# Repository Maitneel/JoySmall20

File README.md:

# JoySmall20
ちょっとしたショートカットやマウス操作をすることを目的に作られた100x95.25mmのキーボードです。

20個のキーとジョイスティック、ロータリーエンコーダを搭載しています。

## Build Guide
必要な部品は以下の通りです

|部品名|個数|遊舎工房さんの商品ページ|秋月電子さんの商品ページ||
|:---|---|---|---|---|
|ProMicro|1|https://shop.yushakobo.jp/products/3905 <br> https://shop.yushakobo.jp/products/pro-micro||いずれか1つで大丈夫です。個人的にはType-Cの方がおすすめです|
|Cherry MX 互換スイッチ|0~20|||つけたい個数用意してください。ProMicroを表側につける場合は最大で18個になります|
|Kailh Switch Socket|スイッチと同じ個数|https://shop.yushakobo.jp/products/a01ps||なくても大丈夫です。MX用を購入してください|
|ダイオード (1N4148)|スイッチと同じ個数|https://shop.yushakobo.jp/products/a0800di-01-100|https://akizukidenshi.com/catalog/g/g100941/||
|ジョイスティック|1||https://akizukidenshi.com/catalog/g/g115951||
|ロータリーエンコーダー|1|https://shop.yushakobo.jp/products/3762|https://akizukidenshi.com/catalog/g/g105772/<br>https://akizukidenshi.com/catalog/g/g105769/<br>https://akizukidenshi.com/catalog/g/g105770/<br>https://akizukidenshi.com/catalog/g/g105771/|EC12と互換性があれば大丈夫だと思います。個人的にはLEDがついてるやつがおすすめです。動作確認は赤・青のLED付きのもので行ってます。1色、フルカラーのLEDが付いてるものがありますが、穴の位置、配線の実装の関係で対応できません|
|LED|0~3|||ロータリーエンコーダでLED付きのものを使用しない場合2つ、ジョイスティックのセンタープッシュを利用しない場合追加で1つのLEDをつけることができます|
|LED用抵抗|LEDと同じ個数|||使用するLEDに合わせて必要な抵抗値を計算してください|
|ジョイスティックセンタープッシュのジャンパー用抵抗|0~1|||あまりに高い抵抗値でなければなんでも大丈夫だと思います。ジャンパーできればいいのでワイヤーでも大丈夫です|
|RESET用タクトスイッチ|1|https://shop.yushakobo.jp/products/a1600ed-01-1|https://akizukidenshi.com/catalog/g/g114890/<br>https://akizukidenshi.com/catalog/g/g114891/||
|コンデンサ|0~2|||ロータリーエンコーダーのノイズ対策につけることができます。プログラムで対応する場合はつけなくて大丈夫です|
|3.5mm TRSジャック|0~1|https://shop.yushakobo.jp/products/a0800tr-01-1|https://akizukidenshi.com/catalog/g/g106070/|通信できたら面白そうだなと思って基板設計ではつけましたが、今のところ対応してないのでただの飾りになる可能性が高いです。|

### 組み立て
撮り忘れたので写真とか動画はないです。正直どの順番でやってもいいのでやりやすい順にやってください。

JoyStickとかRotaryEncoderとかのフットプリントがある方が表で、SW8, SW9から見てJoyStickがある方が上側として説明します。
適時正しく接続ができているか確認してください。

1. ダイオードを半田付けします。フットプリントが四角くなっている方がカソードです。
2. 抵抗を半田付けします。LED1, LED2, LED3に接続する抵抗がそれぞれR1, R2, R3です。LED付きのロータリーエンコーダーを使用する場合R1が基板上部よりのLEDピン、R2が基板Cherryスイッチよりのピンになります。ジョイスティックのセンタープッシュを使用する場合はR4に抵抗(またはワイヤー)を接続してください。
LED3とジョイスティックのセンタープッシュについては同じピンを使用しています。そのため同時に使用することはできませんので、R3とR4を両方とも取り付けることはしないでください。
3. Kailh Switch Socketを取り付ける場合は半田付けする
4. (つける場合は)LED, TRRSジャック, RESET用のタクトスイッチを半田付けする。
-----
ProMicroを裏面につける場合

どちらにつける場合も共通で、一番上のSW3よりのピンがTXO、一番上のJoyStickよりのピンがRAWと接続されるように半田付けします。

5. Kailh Switch Socketを使用しない場合はSW2, SW4を半田付する。(ProMicroを取り付けるのがかなり難しくなるのでSW2, SW4についてはSocketを使うことをおすすめします)
6. ProMicroにピンヘッダを半田付けする。このとき、ProMicroのUSBコネクタがある面からピンヘッダを差し込み、USBコネクタがない面から半田付してください。
7. USBコネクタが上側に来るようにProMicroを基盤に半田付けする。(ピンの位置に注意してください)
2.56mmのピンヘッダを使用し、使用する場合Socketと干渉すると思うので、長めのピンヘッダを使うか、ピンヘッダの絶縁体部分を取り外すか別のピンヘッダの絶縁体部分を用意し、端の部分を2つ重ねて高さを稼ぐなどしてください
------
ProMicroを表面につける場合

どちらにつける場合も共通で、一番上のSW3よりのピンがTXO、一番上のJoyStickよりのピンがRAWと接続されるように半田付けします。

表面に取り付ける場合SW2, SW4は使用できません。

5. ProMicroにピンヘッダを半田付けする。このとき、ProMicroのUSBコネクタのない面からピンヘッダを差し込み、USBコネクタがある面から半田付してください。
6. USBコネクタが上側に来るようにProMicroを基盤に半田付けする。(ピンの位置に注意してください)
----
8. Kailh Switch Socketを使用しない場合はCherry MX 互換スイッチを半田付けする
9. ジョイスティック, ロータリーエンコーダーを取り付ける
10. Kailh Switch Socketを取り付けた場合はスイッチをはめ込む

### ファームウェアを書き込む
今のところ自作のファームウェアしかないので、QMK Firmwareなどをを使って書き込みたい場合はいい感じに作ってください。

まず初めにキーマップを作成します。

1. [Keymap Editor](https://maitneel.github.io/JoySmall20/)でキーマップを編集します。割り当てたいキーの位置をクリックしてから割り当てたいキーをクリックすると割り当てられます。LAYERキーは押している間だけレイヤーの切り替えができます。Layoutはロータリーエンコーダーでキーマップの切り替えができます。
2. `Download define_custom_size.h`, `Download define_custom_keymap.ino`のボタンを押し、設定ファイルをダウンロードします。

キーマップの書き込みをします。Arduino IDEが必要になるので、インストールされていない場合はインストールしてください。

3. [ファームウェアのソースコード](https://github.com/Maitneel/JoySmall20/releases/latest)をダウンロードします。(Releaseから好きなものをダウンロードすることもできますが、バグがある可能性があるのでlatestをダウンロードすることをお勧めします)
4. ダウンロードしたソースコードの`define_custom_size.h`と`define_custom_keymap.ino`に2でダウンロードしたファイルに置き換えます。
5. Arduino IDEで`firmwere_srcs/JoySmall20/JoySmall20.ino`を開き、ProMicroに書き込みます。RESETを2回押すとか連打するとかすると書き込みモードになるはずなのでいろいろ試してみてください。

----

一応これで動くはずです。問題があるようでしたらissue等でご連絡ください！

### 免責
このリポジトリに存在するいずれかまたは全てのものを使用して生じたいかなる損害について、作者はいかなる責任も負いません。

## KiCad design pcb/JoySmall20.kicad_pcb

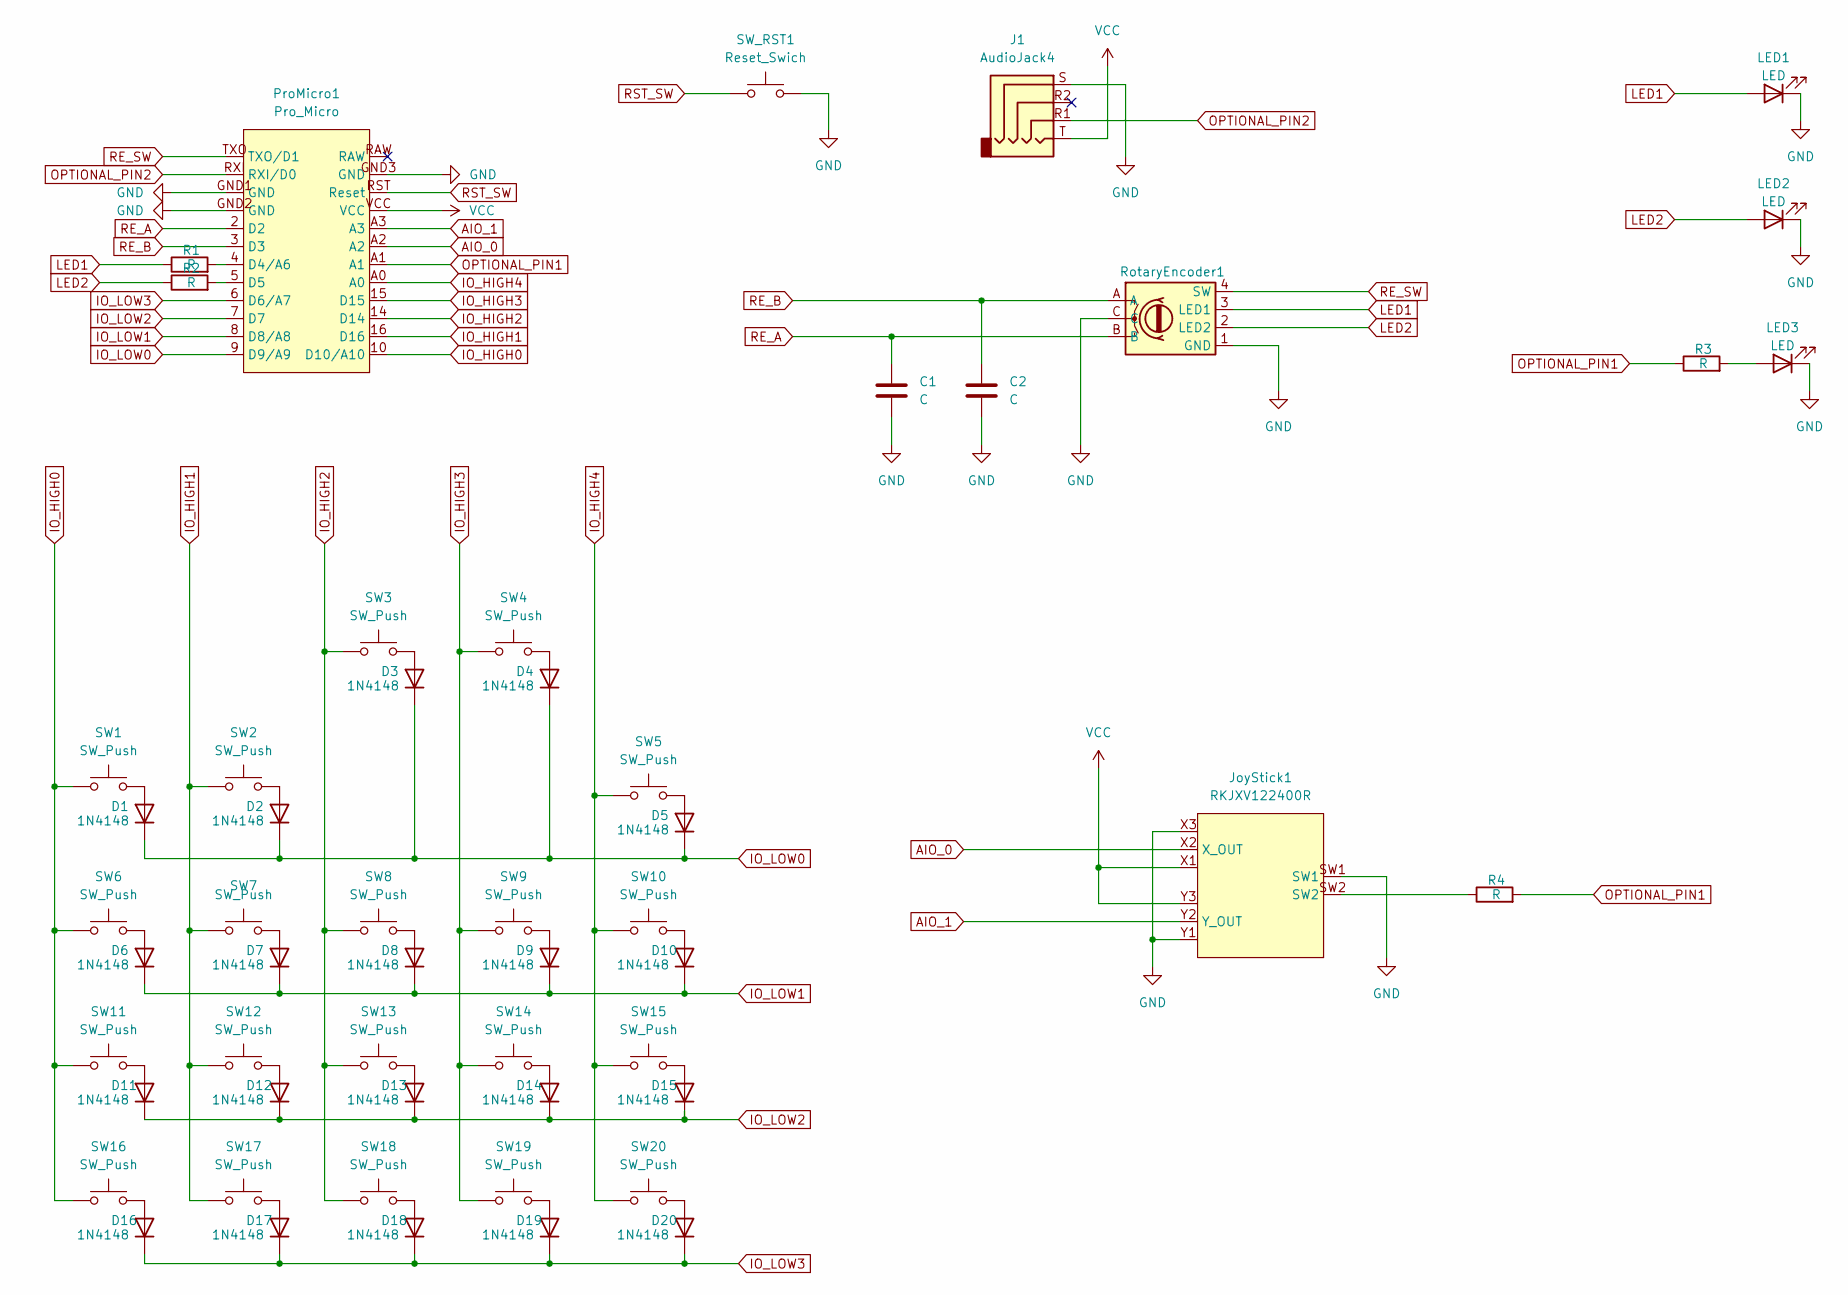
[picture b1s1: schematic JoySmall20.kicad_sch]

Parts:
C1, C2: C; C_Disc_D6.0mm_W2.5mm_P5.00mm
D1, D2, D3, D4, D5, D6, D7, D8, D9, D10, D11, D12, D13, D14, D15, D16, D17, D18, D19, D20: 1N4148
J1: AudioJack4; 3.5mm_audio_jack
JoyStick1: RKJXV122400R
LED1, LED2, LED3: LED; LED_D5.0mm
ProMicro1: Pro_Micro; Pro_Micro_small_pin
R1, R2, R3, R4: R; R_Axial_DIN0207_L6.3mm_D2.5mm_P7.62mm_Horizontal
RotaryEncoder1: RotaryEncoder_with_4pin
SW1, SW2, SW3, SW4, SW5, SW6, SW7, SW8, SW9, SW10, SW11, SW12, SW13, SW14, SW15, SW16, SW17, SW18, SW19, SW20: SW_Push; SW_Cherry_MX_1.00u_PCB_with_kalih_socket_CPG151101S11-16
SW_RST1: Reset_Swich; SW_TactSwitch_THBP07-043CB

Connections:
AIO_0: JoyStick1.X2 (X_OUT), ProMicro1.A2
AIO_1: JoyStick1.Y2 (Y_OUT), ProMicro1.A3
DATA: J1.R1, ProMicro1.RXI (RXI/D0)
GND: C1.2, C2.2, J1.S, JoyStick1.SW1, JoyStick1.X3, JoyStick1.Y1, LED1.1 (K), LED2.1 (K), LED3.1 (K), ProMicro1.GND1 (GND), ProMicro1.GND2 (GND), ProMicro1.GND3 (GND), RotaryEncoder1.1 (GND), RotaryEncoder1.C, SW_RST1.2
IO_HIGH0: ProMicro1.10 (D10/A10), SW1.1, SW6.1, SW11.1, SW16.1
IO_HIGH1: ProMicro1.16 (D16), SW2.1, SW7.1, SW12.1, SW17.1
IO_HIGH2: ProMicro1.14 (D14), SW3.1, SW8.1, SW13.1, SW18.1
IO_HIGH3: ProMicro1.15 (D15), SW4.1, SW9.1, SW14.1, SW19.1
IO_HIGH4: ProMicro1.A0, SW5.1, SW10.1, SW15.1, SW20.1
IO_LOW0: D1.1 (K), D2.1 (K), D3.1 (K), D4.1 (K), D5.1 (K), ProMicro1.9 (D9/A9)
IO_LOW1: D6.1 (K), D7.1 (K), D8.1 (K), D9.1 (K), D10.1 (K), ProMicro1.8 (D8/A8)
IO_LOW2: D11.1 (K), D12.1 (K), D13.1 (K), D14.1 (K), D15.1 (K), ProMicro1.7 (D7)
IO_LOW3: D16.1 (K), D17.1 (K), D18.1 (K), D19.1 (K), D20.1 (K), ProMicro1.6 (D6/A7)
LED1: LED1.2 (A), R1.1, RotaryEncoder1.3 (LED1)
LED2: LED2.2 (A), R2.1, RotaryEncoder1.2 (LED2)
unnamed: D1.2 (A), SW1.2
unnamed: D2.2 (A), SW2.2
unnamed: D3.2 (A), SW3.2
unnamed: D4.2 (A), SW4.2
unnamed: D5.2 (A), SW5.2
unnamed: D6.2 (A), SW6.2
unnamed: D7.2 (A), SW7.2
unnamed: D8.2 (A), SW8.2
unnamed: D9.2 (A), SW9.2
unnamed: D10.2 (A), SW10.2
unnamed: D11.2 (A), SW11.2
unnamed: D12.2 (A), SW12.2
unnamed: D13.2 (A), SW13.2
unnamed: D14.2 (A), SW14.2
unnamed: D15.2 (A), SW15.2
unnamed: D16.2 (A), SW16.2
unnamed: D17.2 (A), SW17.2
unnamed: D18.2 (A), SW18.2
unnamed: D19.2 (A), SW19.2
unnamed: D20.2 (A), SW20.2
unnamed: JoyStick1.SW2, R4.1
unnamed: LED3.2 (A), R3.2
unnamed: ProMicro1.4 (D4/A6), R1.2
unnamed: ProMicro1.5 (D5), R2.2
OPTIONAL_PIN: ProMicro1.A1, R3.1, R4.2
RE_SW: ProMicro1.TXO (TXO/D1), RotaryEncoder1.4 (SW)
RST_SW: ProMicro1.RST (Reset), SW_RST1.1
VCC: J1.T, JoyStick1.X1, JoyStick1.Y3, ProMicro1.VCC

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
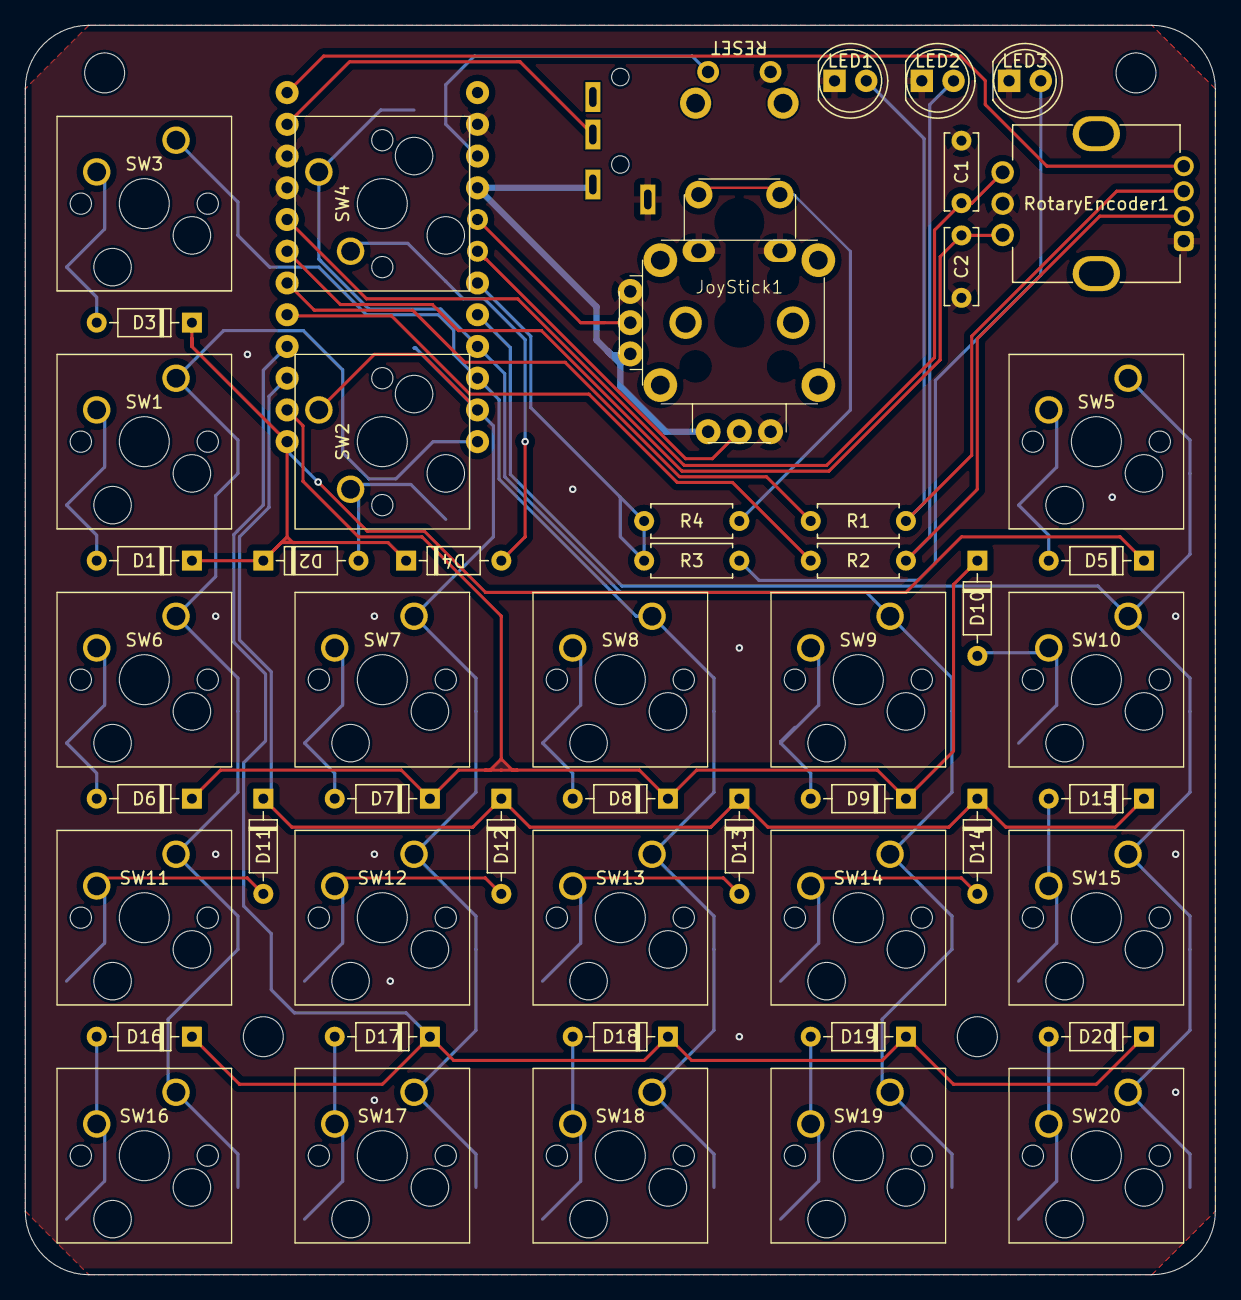
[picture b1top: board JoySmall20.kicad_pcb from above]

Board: 2 copper layers, 95.2 x 100.0 mm, 54 parts (1 on the bottom side), 45 nets.

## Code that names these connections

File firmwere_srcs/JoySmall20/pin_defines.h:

#ifndef INCLUDE_SMALLKEYBOARDV2_2_H_
#define INCLUDE_SMALLKEYBOARDV2_2_H_

#define RE_SW 1
#define OPTIONAL_PIN2 2

#define RE_A 2
#define RE_B 3

#define LED1 4
#define LED2 5

#define IO_LOW3 6
#define IO_LOW2 7
#define IO_LOW1 8
#define IO_LOW0 9

#define AIO1 A3
#define AIO2 A2

#define OPTIONAL_PIN1 A1

#define IO_HIGH4 A0
#define IO_HIGH3 15
#define IO_HIGH2 14
#define IO_HIGH1 16
#define IO_HIGH0 10

#define JOYSTICK_X AIO2
#define JOYSTICK_Y AIO1

#define JOYSTICK_BUTTON OPTIONAL_PIN1

#define JOYSTICK_IGNORE_LENGTH 20
#define JOYSTICK_MAGNIFICATION 20
#define WHEEL_MAGNIFICATION 30

#define UNDEFINED_KEY 0x00

#define MAXIMUM_LAYER_PER_KEYMAP 4
#define MAXIMUM_KEYMAP_COUNT 4

#endif // INCLUDE_SMALLKEYBOARDV2_2_H_

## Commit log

2025-04-13 feat: implement keymap struct
2025-04-13 feat: split file
2025-04-13 feat: rotary encoder lib
2025-04-14 feat: add valiable of joystick button of mouse keymap
2025-04-14 feat: キーボードの通信関係を制御するクラスを追加
2025-04-15 feat: キーボード、 マウスの入力を送信する機構を実装
2025-04-17 restructure
2025-04-17 feat: add makefile of genarator tools for firmwere of keyboard
2025-04-17 rename
2025-04-17 feat: 大まかな処理
2025-04-17 change: 出力先の指定方法を変更
2025-10-13 feat: keymap-editorの枠組みを実装
2025-10-14 feat: レイヤー機能を実装
2025-10-14 rename: layer-set -> layout
2025-10-14 feat: layout機能を実装
2025-10-18 refactor: ファイル分割
2025-10-18 feat: joystickのモードに関する設定項目を追加
2025-10-18 feat: マウスのボタンを追加、マウスとキーを区別しないように変更
2025-10-19 feat: localstorageにJSONでデータを保存し、ページがリロードされた場合でも状態を保持できるように変更
2025-10-19 feat: 設定できるキーに N/A を追加
2025-10-19 refactor: interface 'Key' を使用しないように変更
2025-10-19 feat: JSONをダウンロードするボタンを追加
2025-10-19 feat: jsonをもとにインポートするボタンを追加
2025-10-19 feat: defined_keymap.hを出力する関数を作成
2025-10-19 feat: ファイル構成を変更
2025-10-19 Update Jekyll workflow to include npm build steps
    Added npm install and build steps before Jekyll build.
2025-10-19 Add defaults for working directory in workflow
2025-10-19 Delete build-tools directory
    CLIで作ろうとしていた過去の遺物なので削除
2025-10-20 feat: readmeを追加
2025-10-20 feat: 基板データを追加
2025-10-20 feat: 矢印キーがそんざいしなかったので追加
2025-10-20 fix: 出力が正しくできてなかった問題
2025-10-21 feat: ジョイスティック関係の計算式を修正
2025-10-23 fix: レイアウトを切り替えたときに正しくレイヤーが切り替えられなかった問題
2025-10-23 feat: releaseを使用してファームウェアのソースをダウンロードするように変更
2025-10-23 fix: urlが間違っていた問題
2025-10-23 change: 実行タイミングにパスフィルターを追加
2025-11-09 fix: カーソルの移動量が0の場合でもメッセージを送っていた問題
2025-11-09 fix: 依存関係が正しく設定できていなかった問題
2025-11-09 temp: workflowが正しく動作するか見たいのでサンプルのコードを変更
